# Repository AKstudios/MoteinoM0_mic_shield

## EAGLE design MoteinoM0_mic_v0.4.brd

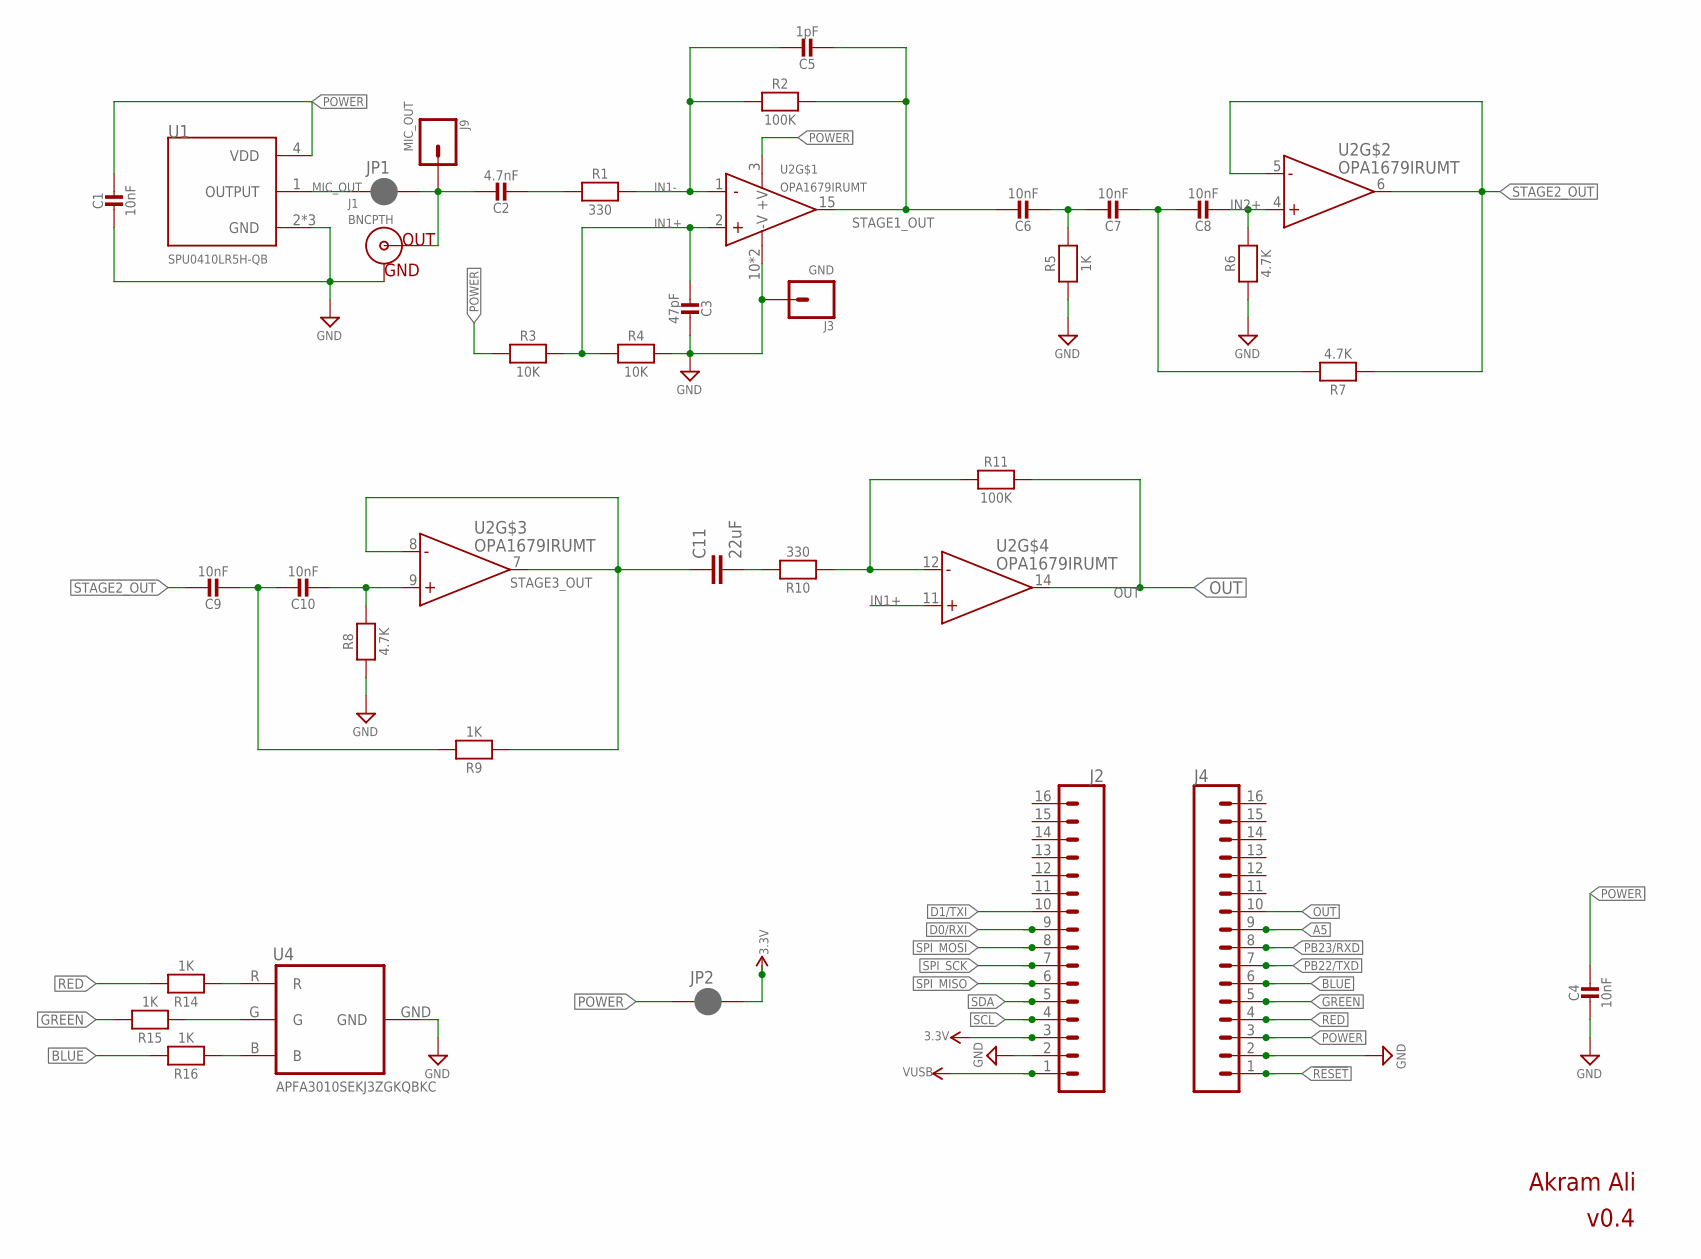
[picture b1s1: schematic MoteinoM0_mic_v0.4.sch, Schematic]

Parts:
C1, C4, C6, C7, C8, C9, C10: 10nF; MICROBUILDER__0402MP; MPN GRM155R71H104KE14J
C2: 4.7nF; MICROBUILDER__0402MP; MPN GRM155R71H104KE14J
C3: 47pF; MICROBUILDER__0402MP; MPN GRM155R71H104KE14J
C5: 1pF; MICROBUILDER__0402MP; MPN GRM155R71H104KE14J
C11: 22uF; 0805
J1: BNCPTH; BNC
J2, J4: CONN_161X16_NO_SILK; 1X16_NO_SILK
J3: GND; 1X01
J9: MIC_OUT; 1X01
JP1, JP2: JUMPER-SMT_2_NC_PASTE_SILK; SMT-JUMPER_2_NC_PASTE_SILK
R1, R10: 330; MICROBUILDER__0402MP; MPN RC0402FR-074K7P
R2, R11: 100K; MICROBUILDER__0402MP; MPN RC0402FR-074K7P
R3, R4: 10K; MICROBUILDER__0402MP; MPN RC0402FR-074K7P
R5, R9, R14, R15, R16: 1K; MICROBUILDER__0402MP; MPN RC0402FR-074K7P
R6, R7, R8: 4.7K; MICROBUILDER__0402MP; MPN RC0402FR-074K7P
U1: SPU0410LR5H-QB; XDCR_SPU0410LR5H-QB
U2: OPA1679IRUMT; QFN65P400X400X80-17N
U4: APFA3010SEKJ3ZGKQBKC; SMD-RA-4

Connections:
3.3V: J2.3, JP2.2
!RESET: J4.1
A5: J4.9
BLUE: J4.6, R16.2
D0/RXI: J2.9
D1/TXI: J2.10
GND: C1.2, C3.1, C4.2, J1.GND, J2.2, J3.1, J4.2, R4.2, R5.1, R6.1, R8.1, U1.2 (GND), U1.3 (GND), U1.5 (GND), U2.10 (-V), U2.17 (-V), U4.GND
GREEN: J4.5, R15.2
IN1+: C3.2, R3.2, R4.1, U2.2 (+IN), U2.11 (+IN)
IN1-: C5.1, R1.2, R2.1, U2.1 (-IN)
IN2+: C8.2, R6.2, U2.4 (+IN)
MIC_OUT: C2.1, J1.S (OUT), J9.1, JP1.2
unnamed: C9.2, C10.1, R9.2
unnamed: C6.2, C7.1, R5.2
unnamed: C7.2, C8.1, R7.2
unnamed: C2.2, R1.1
unnamed: R14.1, U4.R
unnamed: C10.2, R8.2, U2.9 (+IN)
unnamed: C11.2, R10.2
unnamed: R15.1, U4.G
unnamed: R10.1, R11.1, U2.12 (-IN)
unnamed: R16.1, U4.B
unnamed: JP1.1, U1.1 (OUTPUT)
OUT: J4.10, R11.2, U2.14 (OUT)
PB22/TXD: J4.7
PB23/RXD: J4.8
POWER: C1.1, C4.1, J4.3, JP2.1, R3.1, U1.4 (VDD), U2.3 (+V)
RED: J4.4, R14.2
SCL: J2.4
SDA: J2.5
SPI_MISO: J2.6
SPI_MOSI: J2.8
SPI_SCK: J2.7
STAGE1_OUT: C5.2, C6.1, R2.2, U2.15 (OUT)
STAGE2_OUT: C9.1, R7.1, U2.5 (-IN), U2.6 (OUT)
STAGE3_OUT: C11.1, R9.1, U2.7 (OUT), U2.8 (-IN)
VUSB: J2.1

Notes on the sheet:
v0.4
Akram Ali

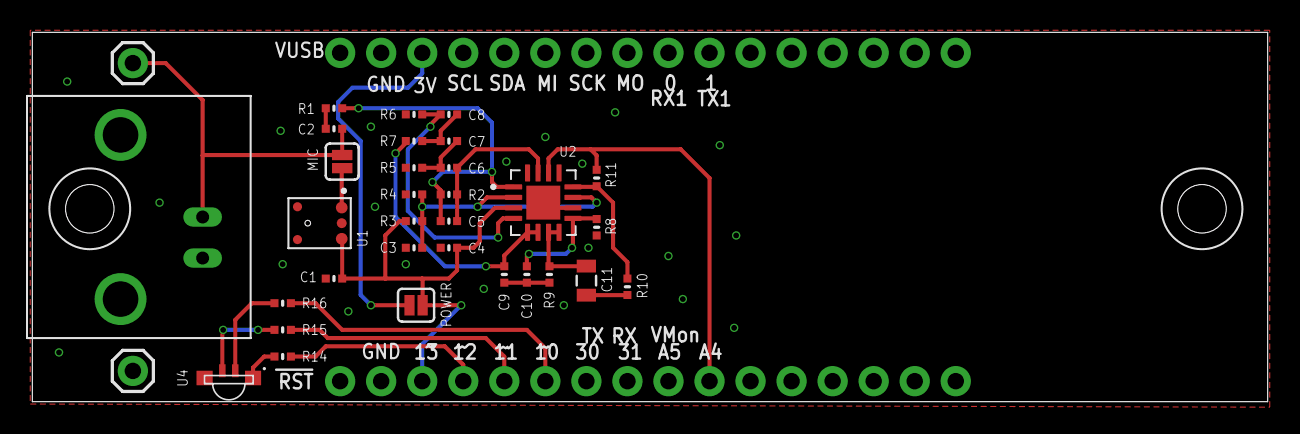
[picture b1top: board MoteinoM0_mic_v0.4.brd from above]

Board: 2 copper layers, 76.4 x 22.9 mm, 35 parts (0 on the bottom side), 25 nets.

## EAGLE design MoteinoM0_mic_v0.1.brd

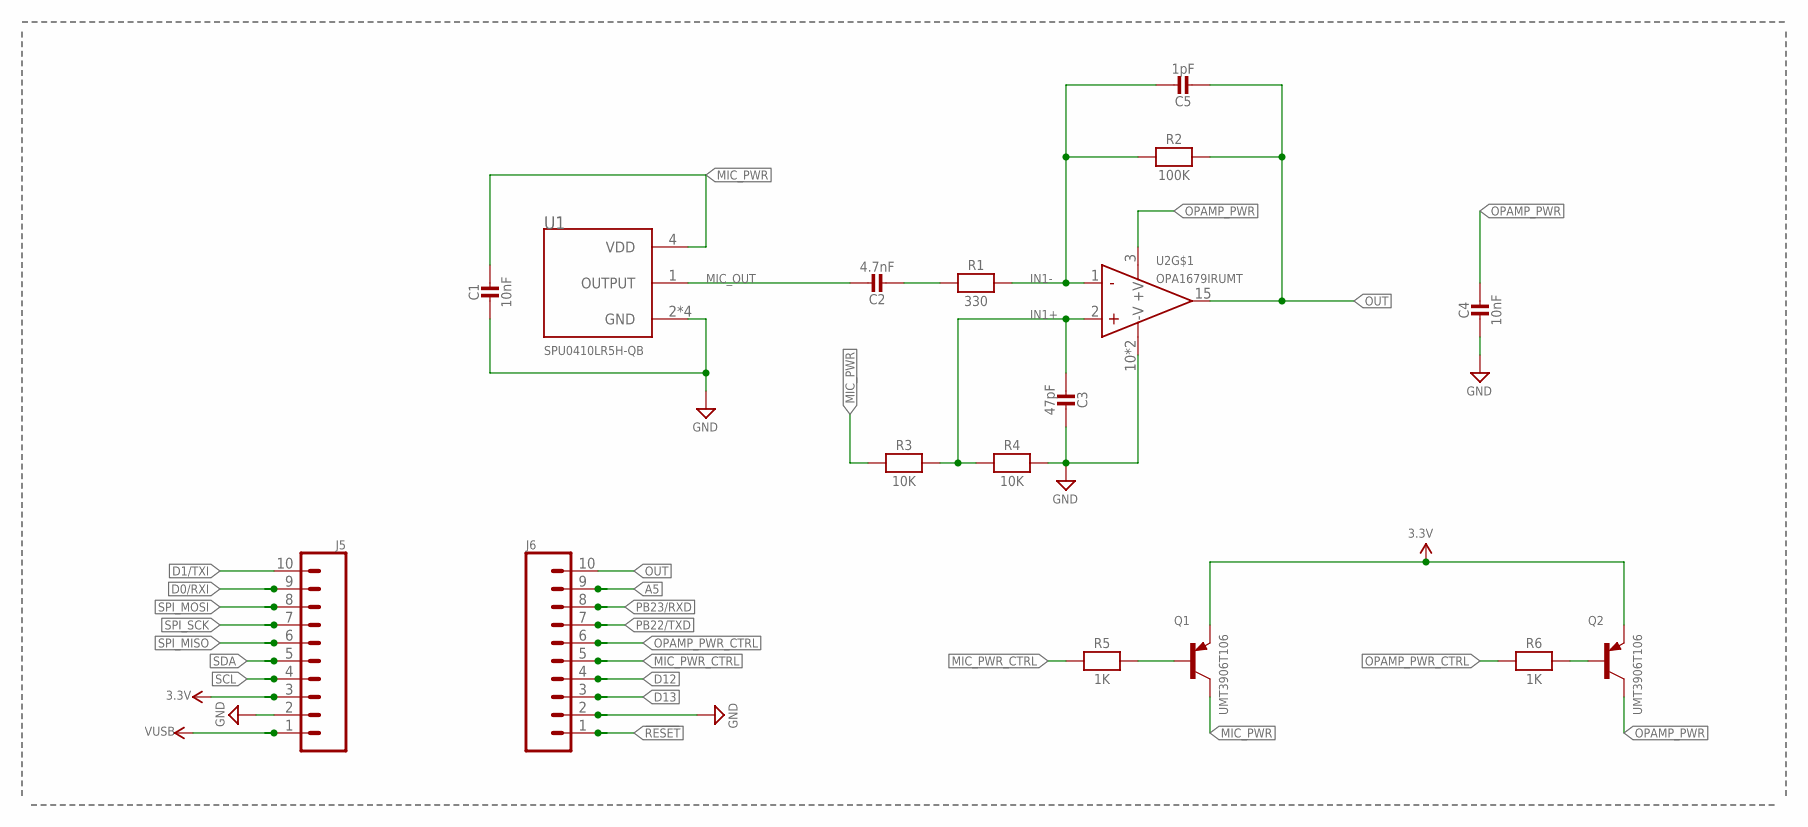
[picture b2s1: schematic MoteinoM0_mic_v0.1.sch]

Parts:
C1, C4: 10nF; MICROBUILDER__0402MP; MPN GRM155R71H104KE14J
C2: 4.7nF; MICROBUILDER__0402MP; MPN GRM155R71H104KE14J
C3: 47pF; MICROBUILDER__0402MP; MPN GRM155R71H104KE14J
C5: 1pF; MICROBUILDER__0402MP; MPN GRM155R71H104KE14J
J5, J6: CONN_10NO_SILK_PTH_FEMALE; 1X10_NO_SILK
Q1, Q2: UMT3906T106; SOT65P210X100-3N-PNP
R1: 330; MICROBUILDER__0402MP; MPN RC0402FR-074K7P
R2: 100K; MICROBUILDER__0402MP; MPN RC0402FR-074K7P
R3, R4: 10K; MICROBUILDER__0402MP; MPN RC0402FR-074K7P
R5, R6: 1K; MICROBUILDER__0402MP; MPN RC0402FR-074K7P
U1: SPU0410LR5H-QB; XDCR_SPU0410LR5H-QB
U2: OPA1679IRUMT; QFN65P400X400X80-17N

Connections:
3.3V: J5.3, Q1.1 (E), Q2.1 (E)
!RESET: J6.1
A5: J6.9
D0/RXI: J5.9
D1/TXI: J5.10
D12: J6.4
D13: J6.3
GND: C1.2, C3.1, C4.2, J5.2, J6.2, R4.2, U1.2 (GND), U1.3 (GND), U1.5 (GND), U1.6 (GND), U2.10 (-V), U2.17 (-V)
IN1+: C3.2, R3.2, R4.1, U2.2 (+IN)
IN1-: C5.1, R1.2, R2.1, U2.1 (-IN)
MIC_OUT: C2.1, U1.1 (OUTPUT)
MIC_PWR: C1.1, Q1.3 (C), R3.1, U1.4 (VDD)
MIC_PWR_CTRL: J6.5, R5.1
unnamed: Q1.2 (B), R5.2
unnamed: Q2.2 (B), R6.2
unnamed: C2.2, R1.1
OPAMP_PWR: C4.1, Q2.3 (C), U2.3 (+V)
OPAMP_PWR_CTRL: J6.6, R6.1
OUT: C5.2, J6.10, R2.2, U2.15 (OUT)
PB22/TXD: J6.7
PB23/RXD: J6.8
SCL: J5.4
SDA: J5.5
SPI_MISO: J5.6
SPI_MOSI: J5.8
SPI_SCK: J5.7
VUSB: J5.1

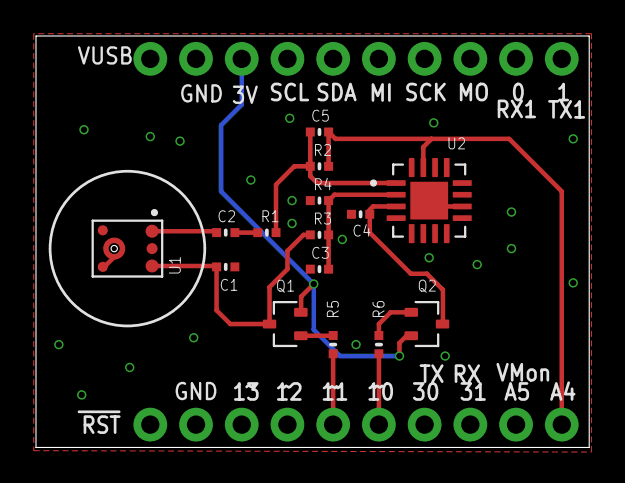
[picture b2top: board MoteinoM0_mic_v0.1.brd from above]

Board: 2 copper layers, 30.7 x 22.9 mm, 17 parts (0 on the bottom side), 13 nets.

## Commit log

2022-03-01 simulation files added
2022-03-16 v0.3 - design update
    - Added butterworth filter for better bandpass filtering
    - Added extra OPAMP for additional gain
    - Merged mic and opamp power into one
    - Added jumper to quickly add 3.3V power
    - Added jumper to add/remove mic when needed
    - Removed unnecessary jumpers
2023-03-24 v0.4
    - removed stage 5
    - board size update
    - header size increased

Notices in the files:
parts and their libraries:
SparkFun-Connectors: Licensing: Creative Commons ShareAlike 4.0 International - https://creativecommons.org/licenses/by-sa/4.0
